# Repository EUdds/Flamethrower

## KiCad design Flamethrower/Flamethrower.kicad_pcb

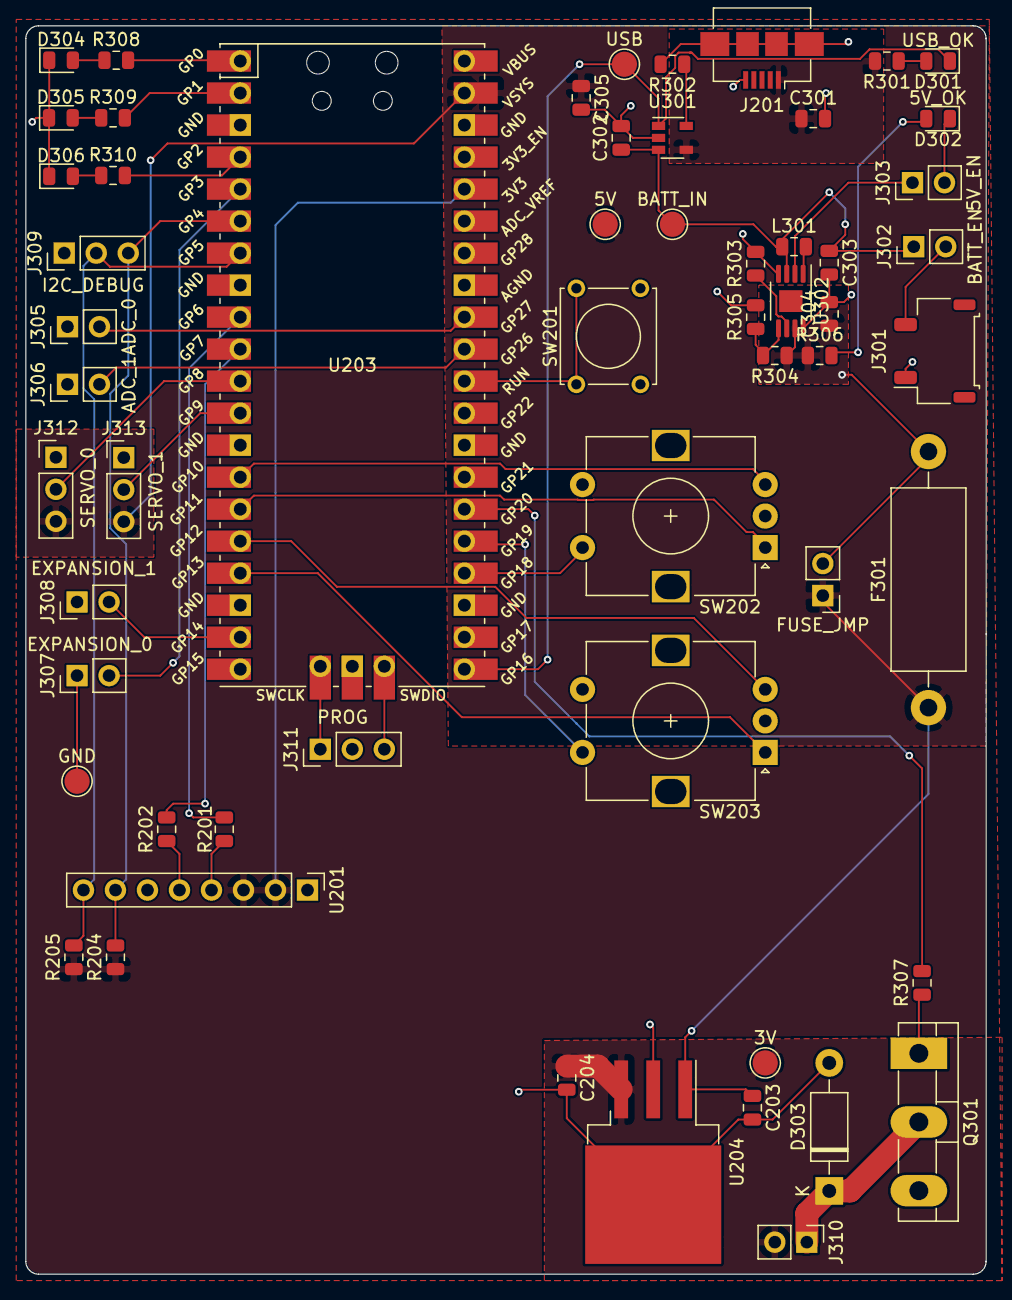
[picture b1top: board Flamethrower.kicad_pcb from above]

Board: 2 copper layers, 76.2 x 99.1 mm, 57 parts (0 on the bottom side), 46 nets.

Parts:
3V: SPRK_TP; TestPoint_Pad_D2.0mm
5V: 5V TP; TestPoint_Pad_D2.0mm
BATT_IN: Batt TestPoint; TestPoint_Pad_D2.0mm
C203: 0.1uF; C_0805_2012Metric
C204, C303, C305: 10uF; C_0805_2012Metric
C301, C302: 4.7uF; C_0805_2012Metric
C304: 22uF; C_0805_2012Metric
D301: USB_OK; LED_0805_2012Metric
D302: 5V_OK; LED_0805_2012Metric
D303: 1N4004; D_DO-41_SOD81_P10.16mm_Horizontal
D304: LED_0; LED_0805_2012Metric
D305: LED_1; LED_0805_2012Metric
D306: LED_2; LED_0805_2012Metric
F301: Fuse; R_Axial_DIN0614_L14.3mm_D5.7mm_P20.32mm_Horizontal
FUSE_JMP: FUSE_BYPASS; PinHeader_1x02_P2.54mm_Vertical
GND: GND TP; TestPoint_Pad_D2.0mm
J201: USB_B_Micro; USB_Micro-B_Amphenol_10104110_Horizontal
J301: JST_2MM_MALE; JST_LEA_SM02B-LEASS-TF_1x02-1MP_P4.20mm_Horizontal
J302: BATT_EN; PinHeader_1x02_P2.54mm_Vertical
J303: 5V_EN; PinHeader_1x02_P2.54mm_Vertical
J305: ADC_0; PinHeader_1x02_P2.54mm_Vertical
J306: ADC_1; PinHeader_1x02_P2.54mm_Vertical
J307: EXPANSION_0; PinHeader_1x02_P2.54mm_Vertical
J308: EXPANSION_1; PinHeader_1x02_P2.54mm_Vertical
J309: I2C_DEBUG; PinHeader_1x03_P2.54mm_Vertical
J310: SPARK; PinHeader_1x02_P2.54mm_Vertical
J311: PROG; PinHeader_1x03_P2.54mm_Vertical
J312: SERVO_0; PinHeader_1x03_P2.54mm_Vertical
J313: SERVO_1; PinHeader_1x03_P2.54mm_Vertical
L301: 2.2uH3A; L_0805_2012Metric
Q301: TIP120; TO-3P-3_Vertical
R201, R202, R303: DNP; R_0805_2012Metric
R204, R205: 4.7k; R_0805_2012Metric
R301, R306, R308, R309, R310: 220; R_0805_2012Metric
R302: 2k; R_0805_2012Metric
R304: 750k; R_0805_2012Metric
R305: 100k; R_0805_2012Metric
R307: 1k; R_0805_2012Metric
SW201: RST; SW_Tactile_Straight_KSA0Axx1LFTR
SW202: Rotary_Encoder_Switch_1; RotaryEncoder_Alps_EC12E-Switch_Vertical_H20mm
SW203: Rotary_Encoder_Switch_0; RotaryEncoder_Alps_EC12E-Switch_Vertical_H20mm
U201: ADXL345-SF; PinHeader_1x08_P2.54mm_Vertical
U203: Pico; RPi_Pico_SMD_TH
U204: LM2937xS; TO-263-3_TabPin2
U301: MCP73831; SOT-23-5
U302: PAM2401; MSOP-8-1EP_3x3mm_P0.65mm_EP1.73x1.85mm
USB: V_USB TestPoint; TestPoint_Pad_D2.0mm

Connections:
3V_SPRK: 3V.1, C204.1, J310.2, U204.3
+3V3: R204.1, R205.1, U201.2, U201.3, U203.36
+5V: 5V.1, C203.1, C305.1, F301.1, FUSE_JMP.1, J312.3, J313.3, U203.39, U204.1
+BATT: BATT_IN.1, C302.1, C303.1, J302.1, L301.1, U301.3, U302.3
/MCU/CHRG_STAT: D301.1, U203.21, U301.1, USB.1
/MCU/Pinouts/LED_0_R: D304.2, R308.1
/MCU/Pinouts/LED_1_R: D305.2, R309.1
/MCU/Pinouts/LED_2_R: D306.2, R310.1
/MCU/Pinouts/SPRK_FET: D303.1, J310.1, Q301.2
/MCU/RST: SW201.1, U203.30
/Sheet600348E6/5V_OK: D302.2, R306.2
/Sheet600348E6/BATT_+: J301.2, J302.2
/Sheet600348E6/BATT_EN: J303.1, U302.2
/Sheet600348E6/BATT_PROG: R302.1, U301.5
/Sheet600348E6/BOOST_OUT: C304.1, F301.2, FUSE_JMP.2, R304.1, R306.1, U302.7
/Sheet600348E6/FB_DIV: R304.2, R305.1, U302.5
/Sheet600348E6/LX_IND: L301.2, U302.1
/Sheet600348E6/RST_N: R303.1, U302.6
/Sheet600348E6/USB_OK: D301.2, R301.1
/Sheet600348E6/V_USB: C301.1, J201.1, R301.2, U301.4
ADC_0: J305.2, U203.32
ADC_1: J306.2, U203.31
EXP_0: J307.2, U203.5
EXP_1: J308.2, U203.19
GND: C203.2, C204.2, C301.2, C302.2, C303.2, C304.2, C305.2, D302.1, D303.2, D304.1, D305.1, D306.1, GND.1, J201.5, J201.6, J301.1, J303.2, J305.1, J306.1, J307.1, J308.1, J309.1, J311.2, J312.1, J313.1, Q301.3, R302.2, R303.2, R305.2, SW201.2, SW202.C, SW202.S2, SW203.C, SW203.S2, U201.1, U201.6, U203.3, U203.8, U203.13, U203.18, U203.23, U203.28, U203.33, U203.38, U203.42, U204.2, U301.2, U302.4, U302.8
I2C_SCL: J309.2, R205.2, U201.8, U203.7
I2C_SDA: J309.3, R204.2, U201.7, U203.6
IMU_INT1: R201.1, U203.9
IMU_INT2: R202.2, U203.10
LED_0: R308.2, U203.1
LED_1: R309.2, U203.2
LED_2: R310.2, U203.4
unnamed: Q301.1, R307.1
unnamed: R201.2, U201.4
unnamed: R202.1, U201.5
ROT_0_CCW: SW203.B, U203.16
ROT_0_CW: SW203.A, U203.17
ROT_0_SW: SW203.S1, U203.25
ROT_1_CCW: SW202.B, U203.14
ROT_1_CW: SW202.A, U203.15
ROT_1_SW: SW202.S1, U203.24
SERVO_0: J312.2, U203.11
SERVO_1: J313.2, U203.12
SPARK_EN: R307.2, U203.26
SWCLK: J311.1, U203.41
SWDIO: J311.3, U203.43

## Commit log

2021-04-06 Move everything to git
2021-04-06 Remove zip files
2021-04-08 Redit the PCB entirely
